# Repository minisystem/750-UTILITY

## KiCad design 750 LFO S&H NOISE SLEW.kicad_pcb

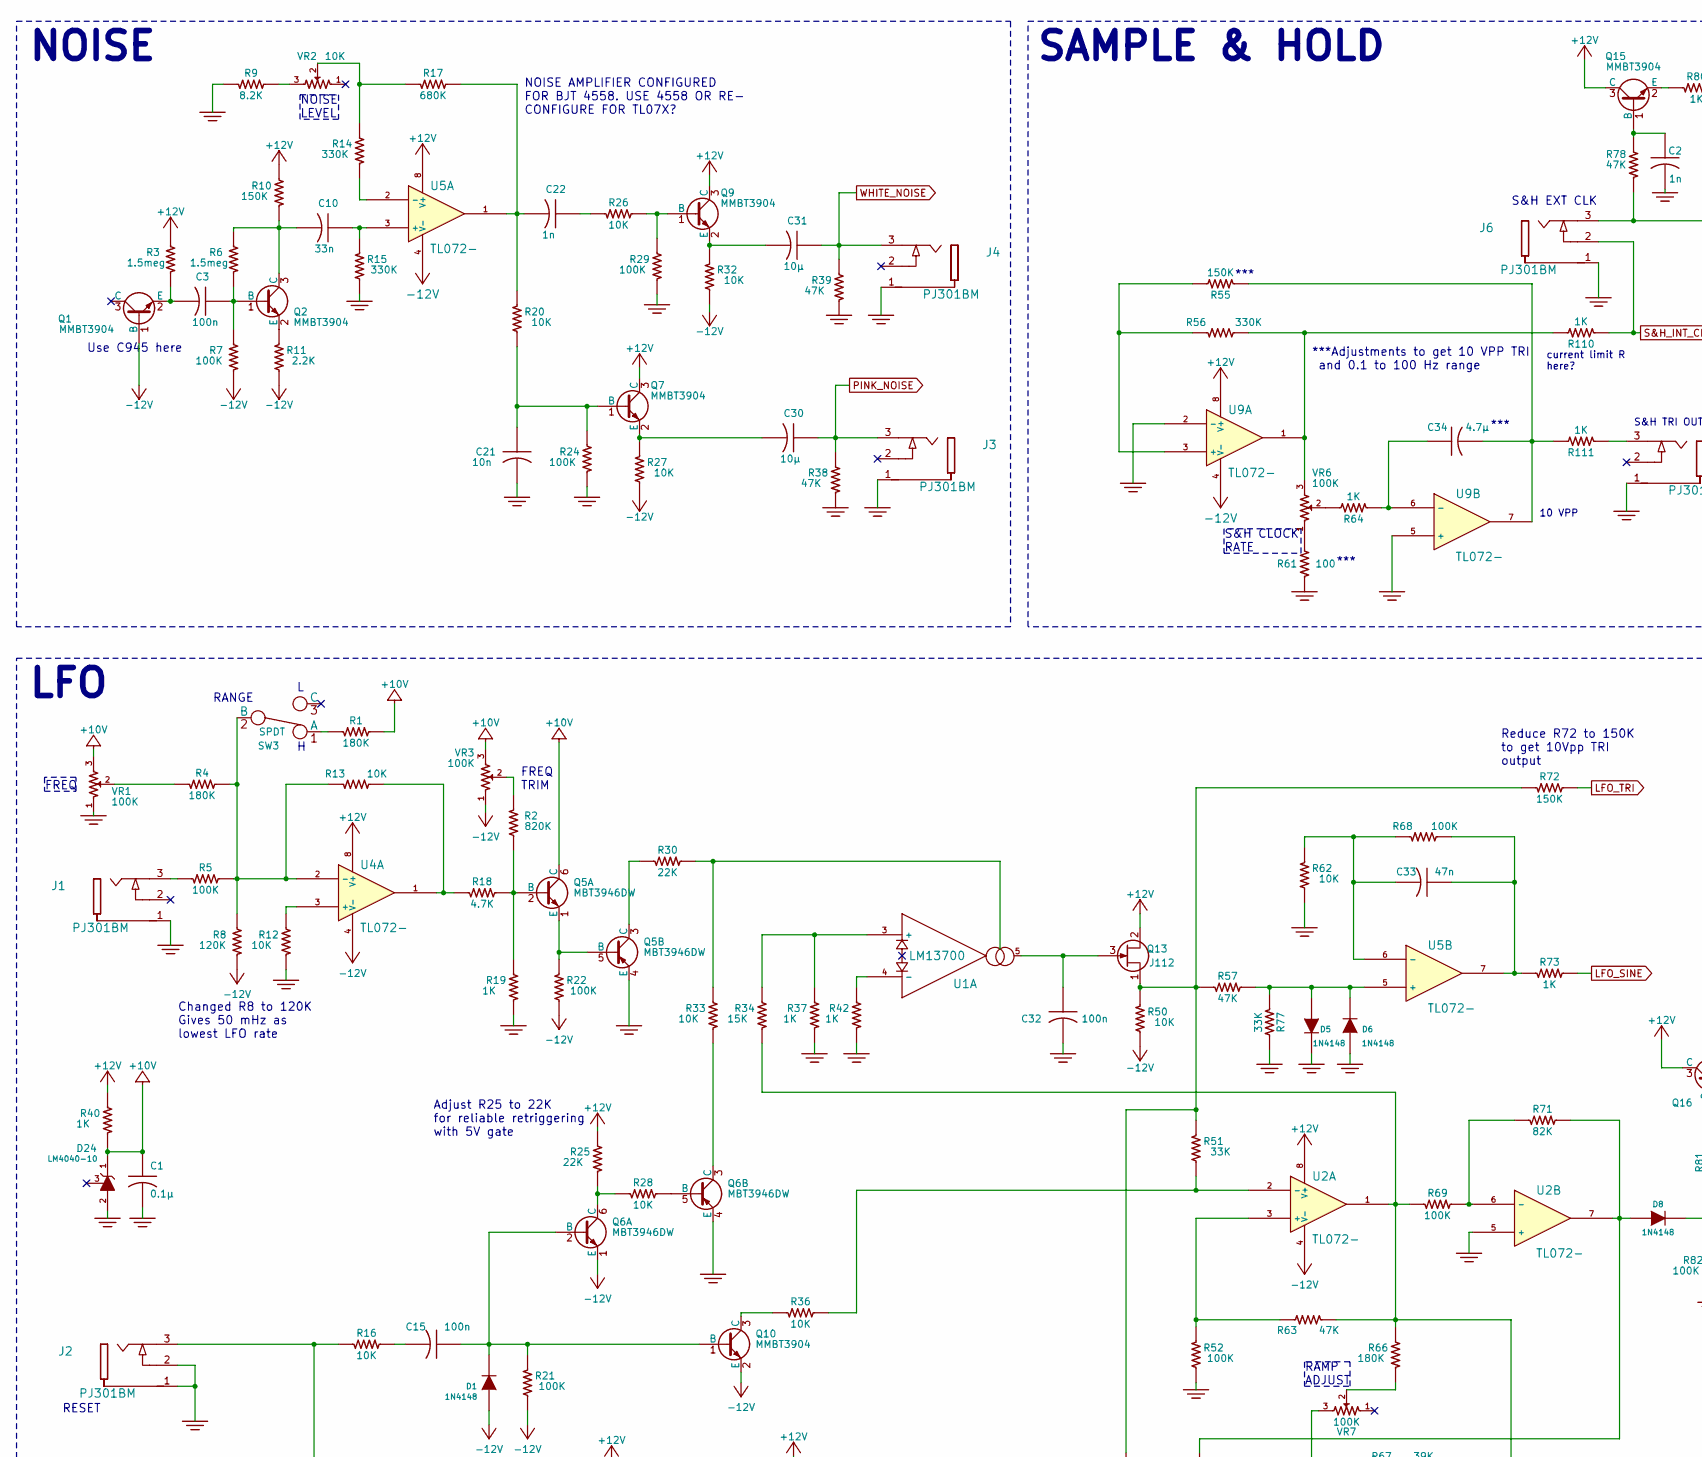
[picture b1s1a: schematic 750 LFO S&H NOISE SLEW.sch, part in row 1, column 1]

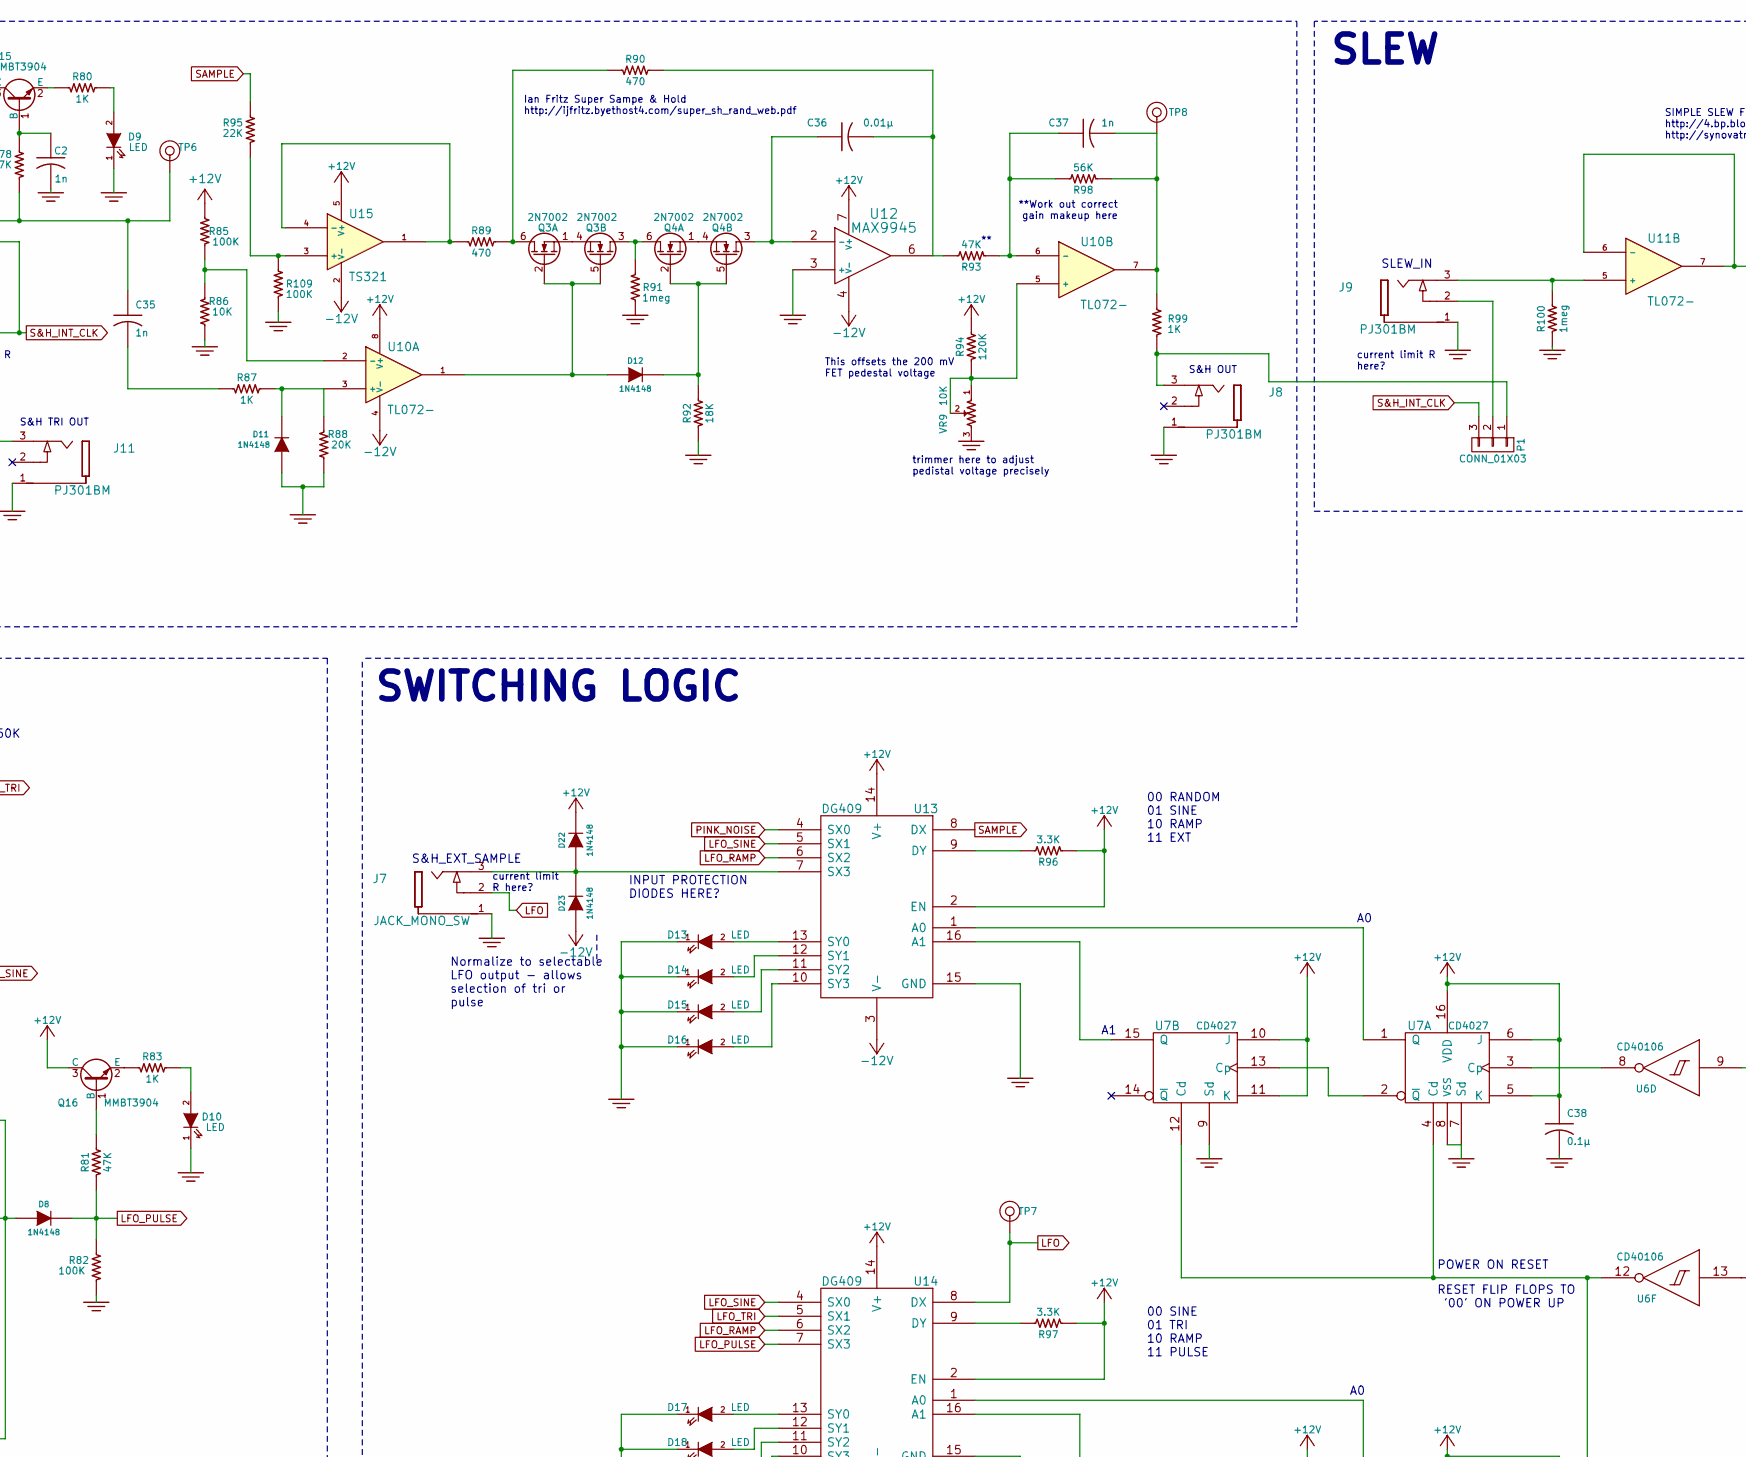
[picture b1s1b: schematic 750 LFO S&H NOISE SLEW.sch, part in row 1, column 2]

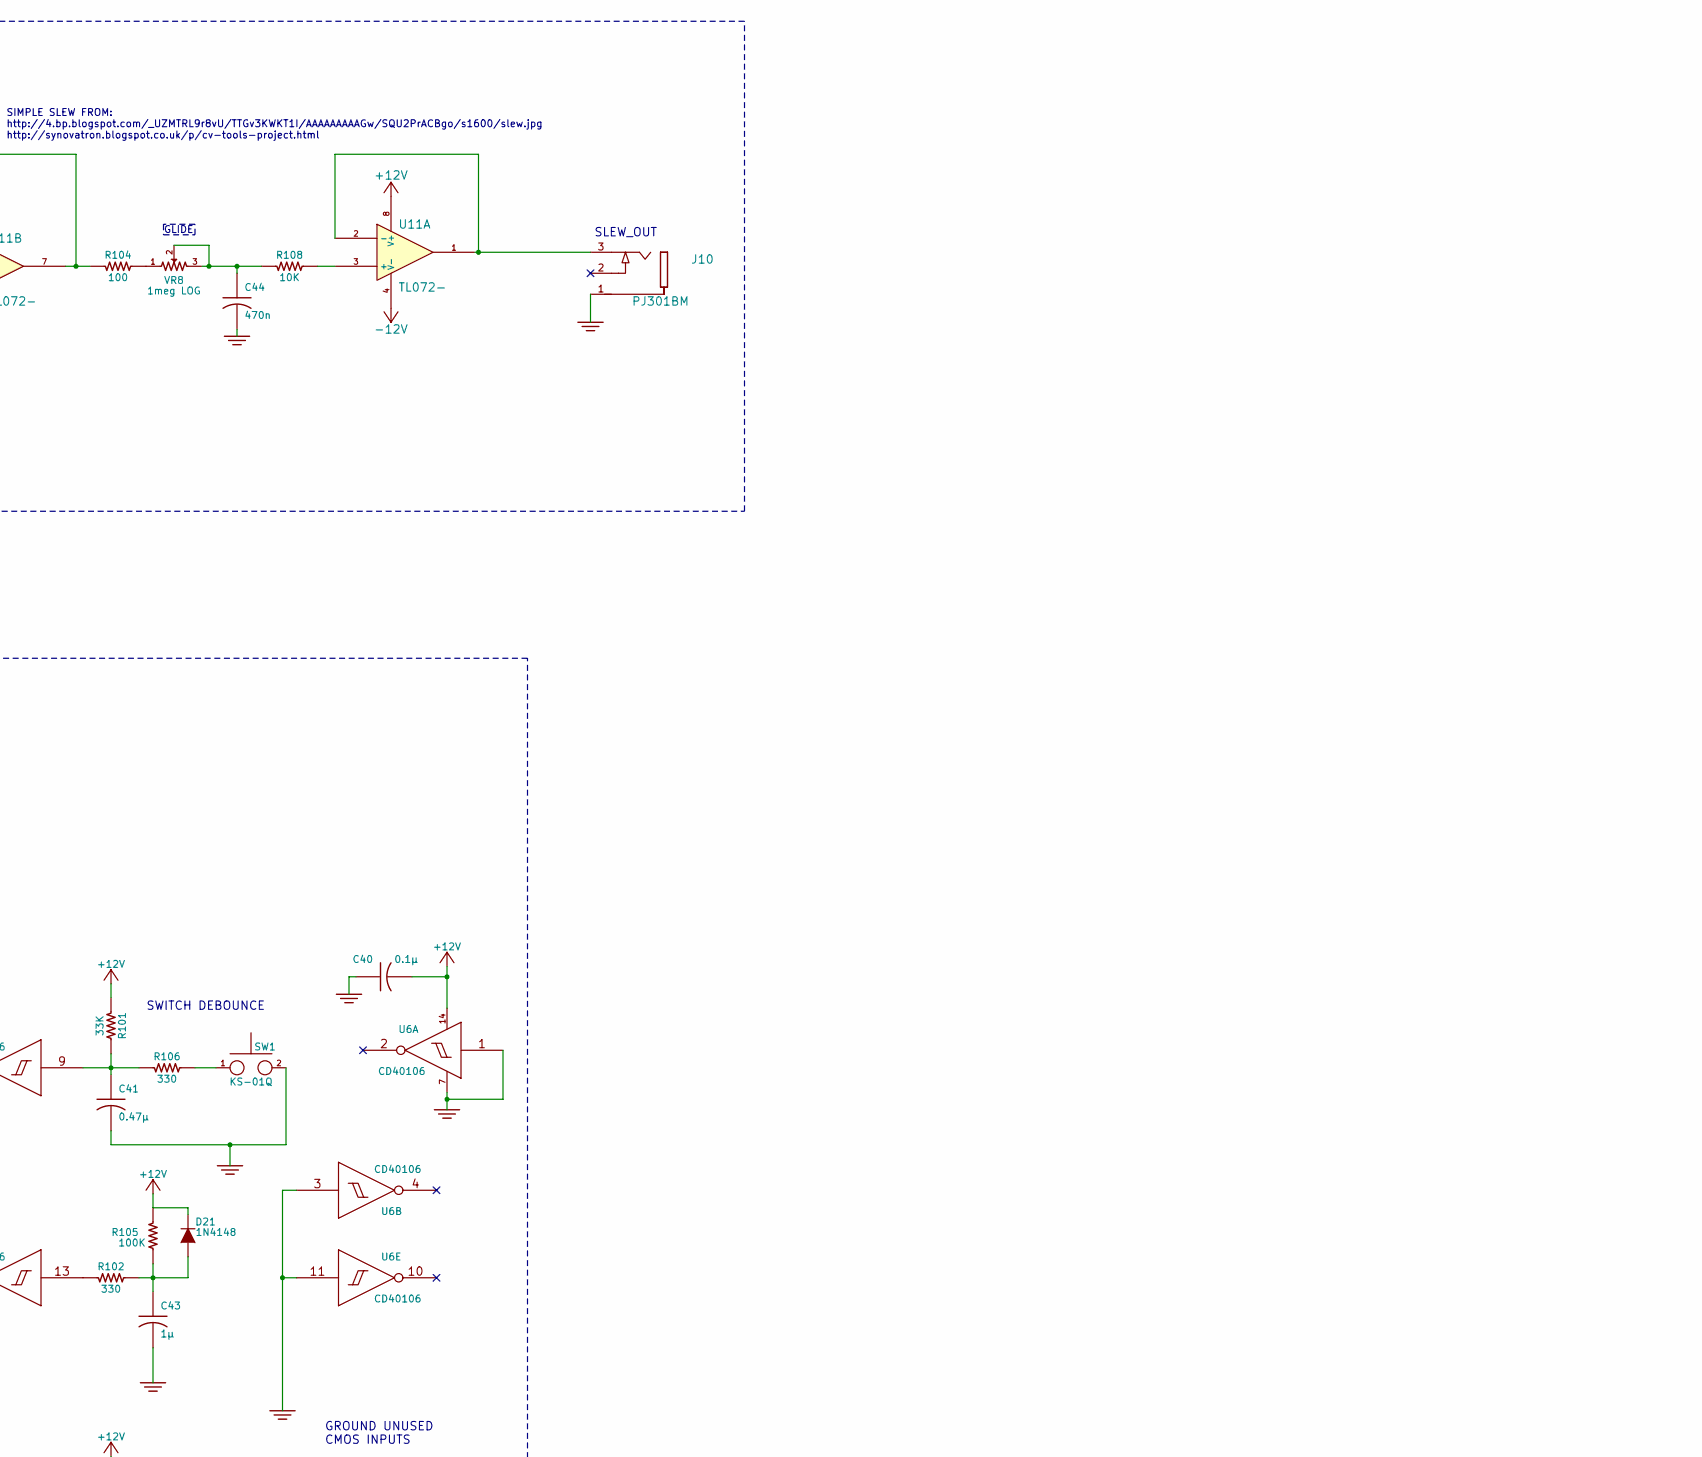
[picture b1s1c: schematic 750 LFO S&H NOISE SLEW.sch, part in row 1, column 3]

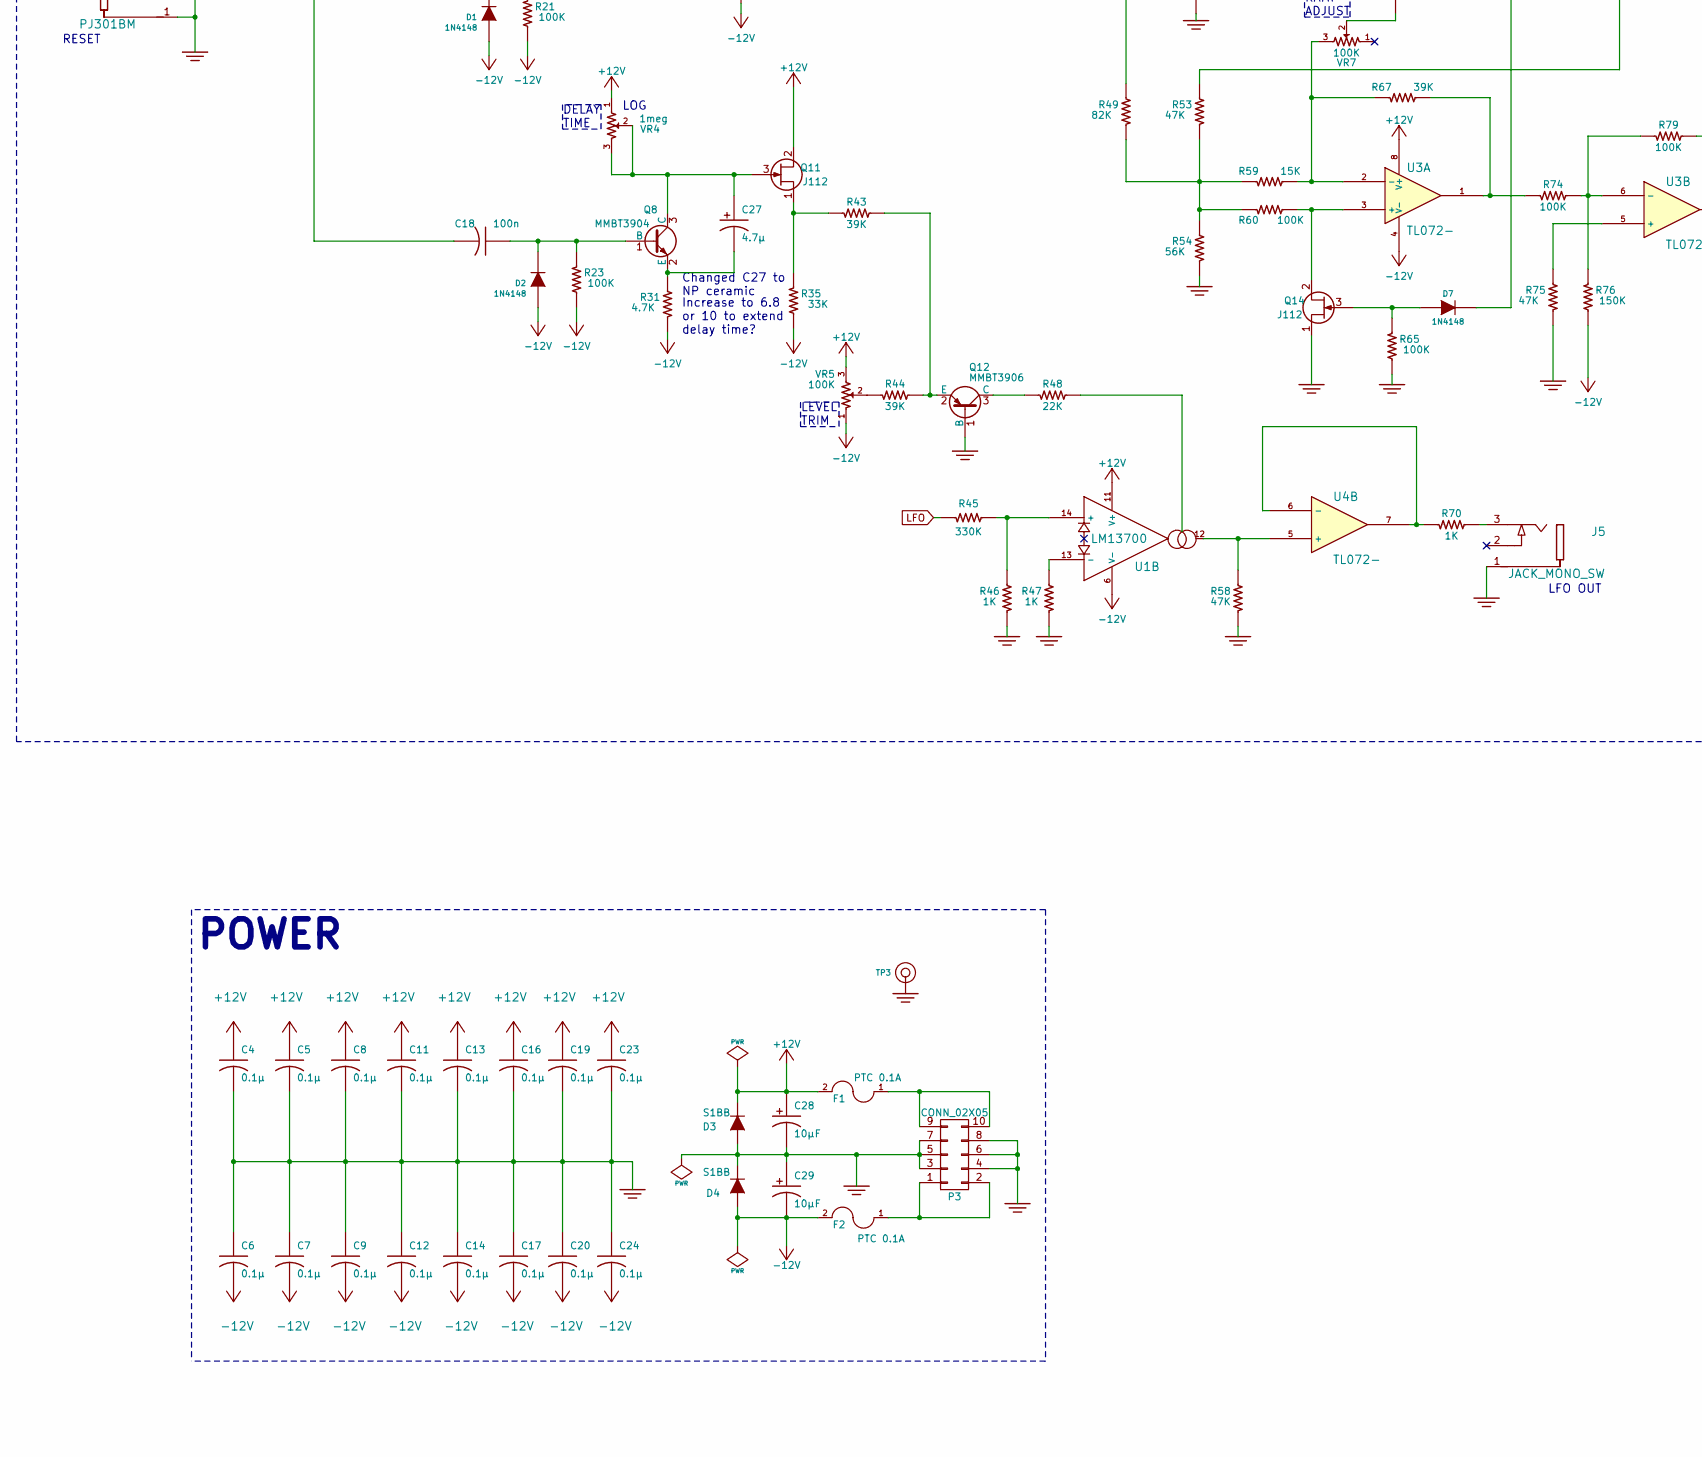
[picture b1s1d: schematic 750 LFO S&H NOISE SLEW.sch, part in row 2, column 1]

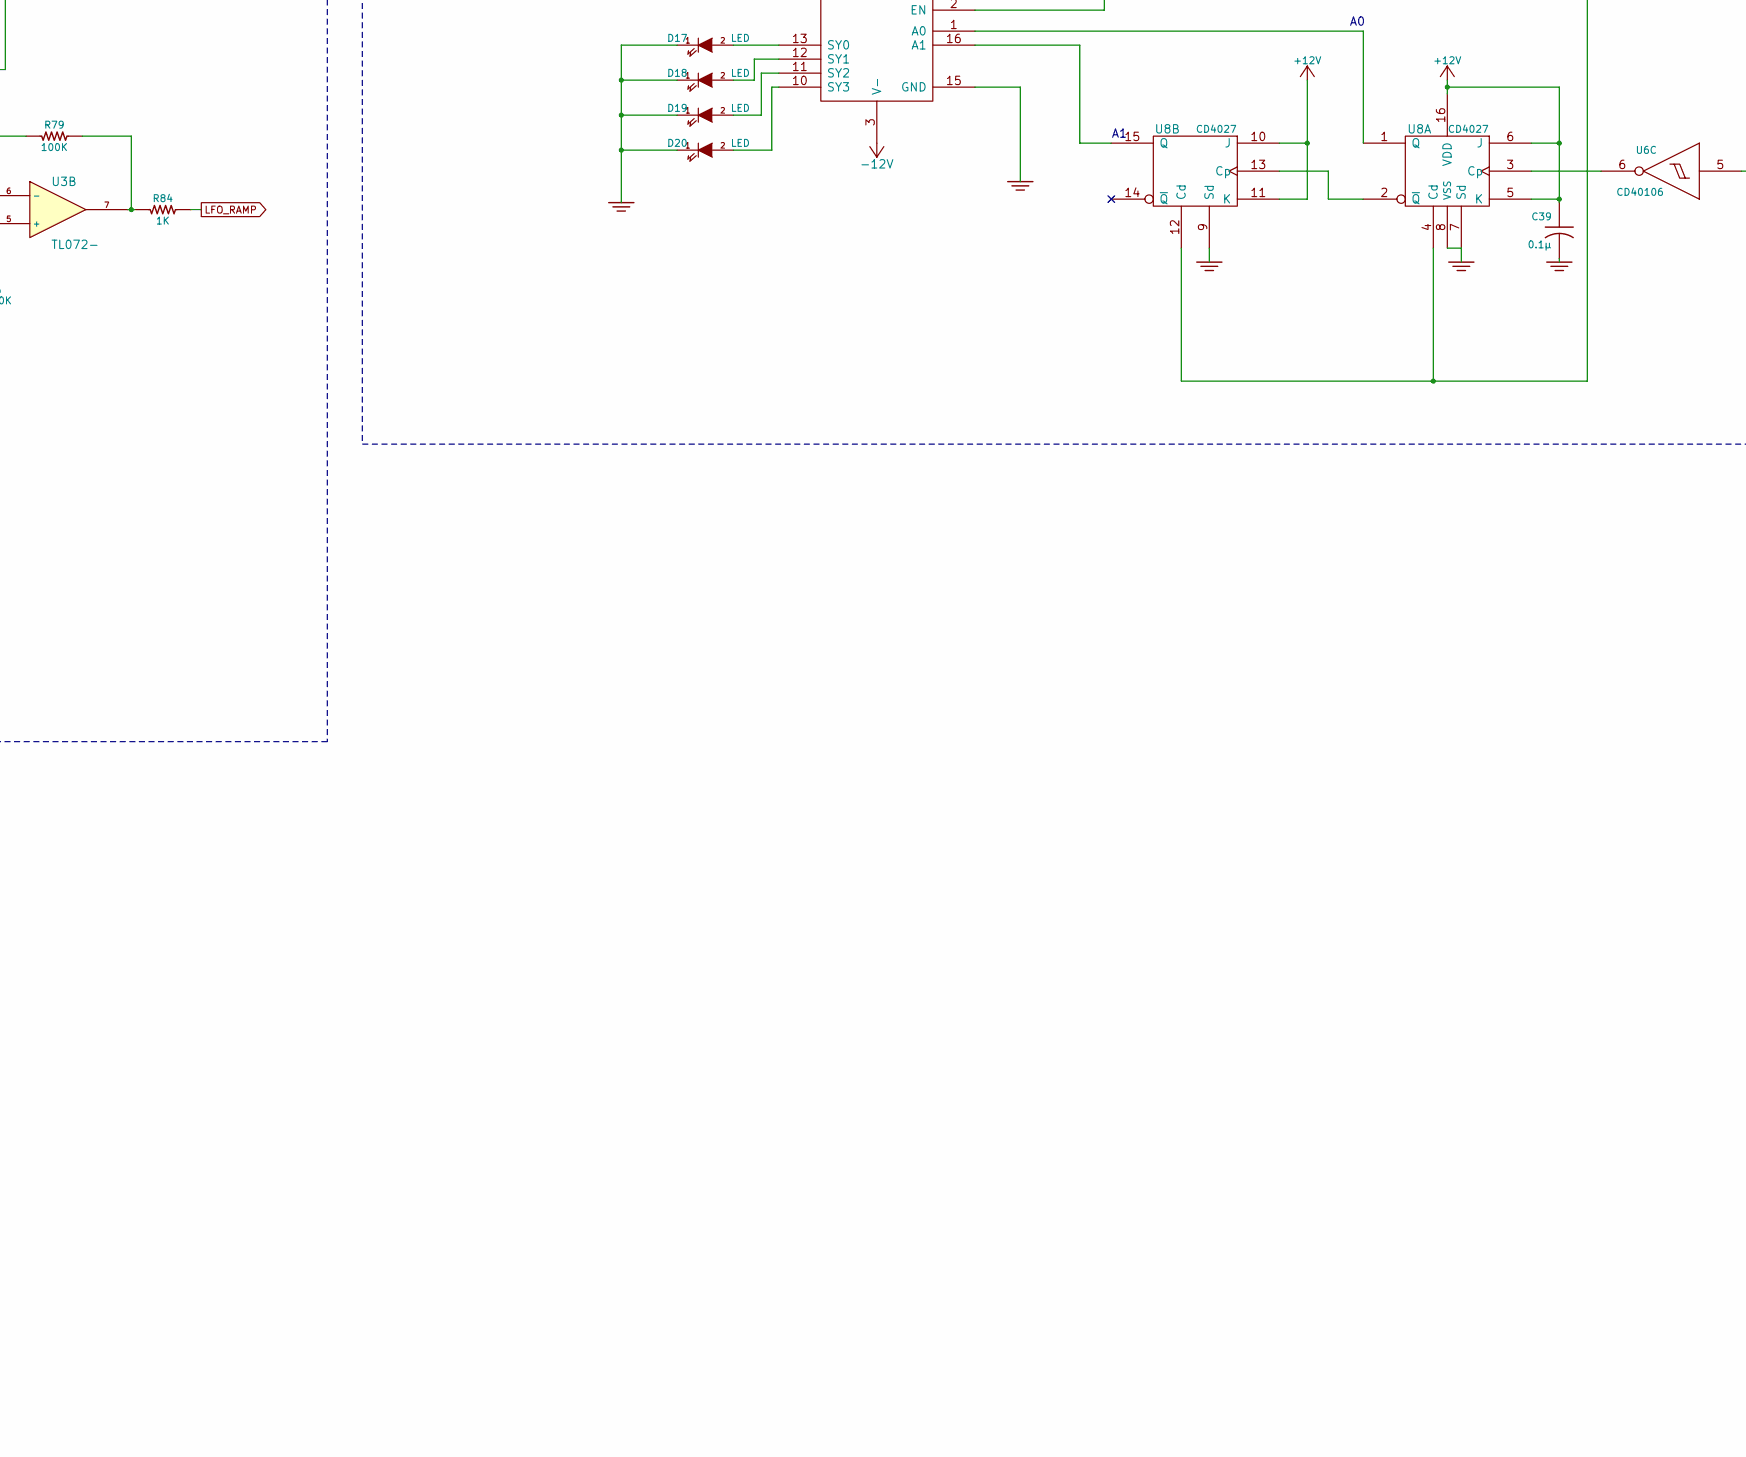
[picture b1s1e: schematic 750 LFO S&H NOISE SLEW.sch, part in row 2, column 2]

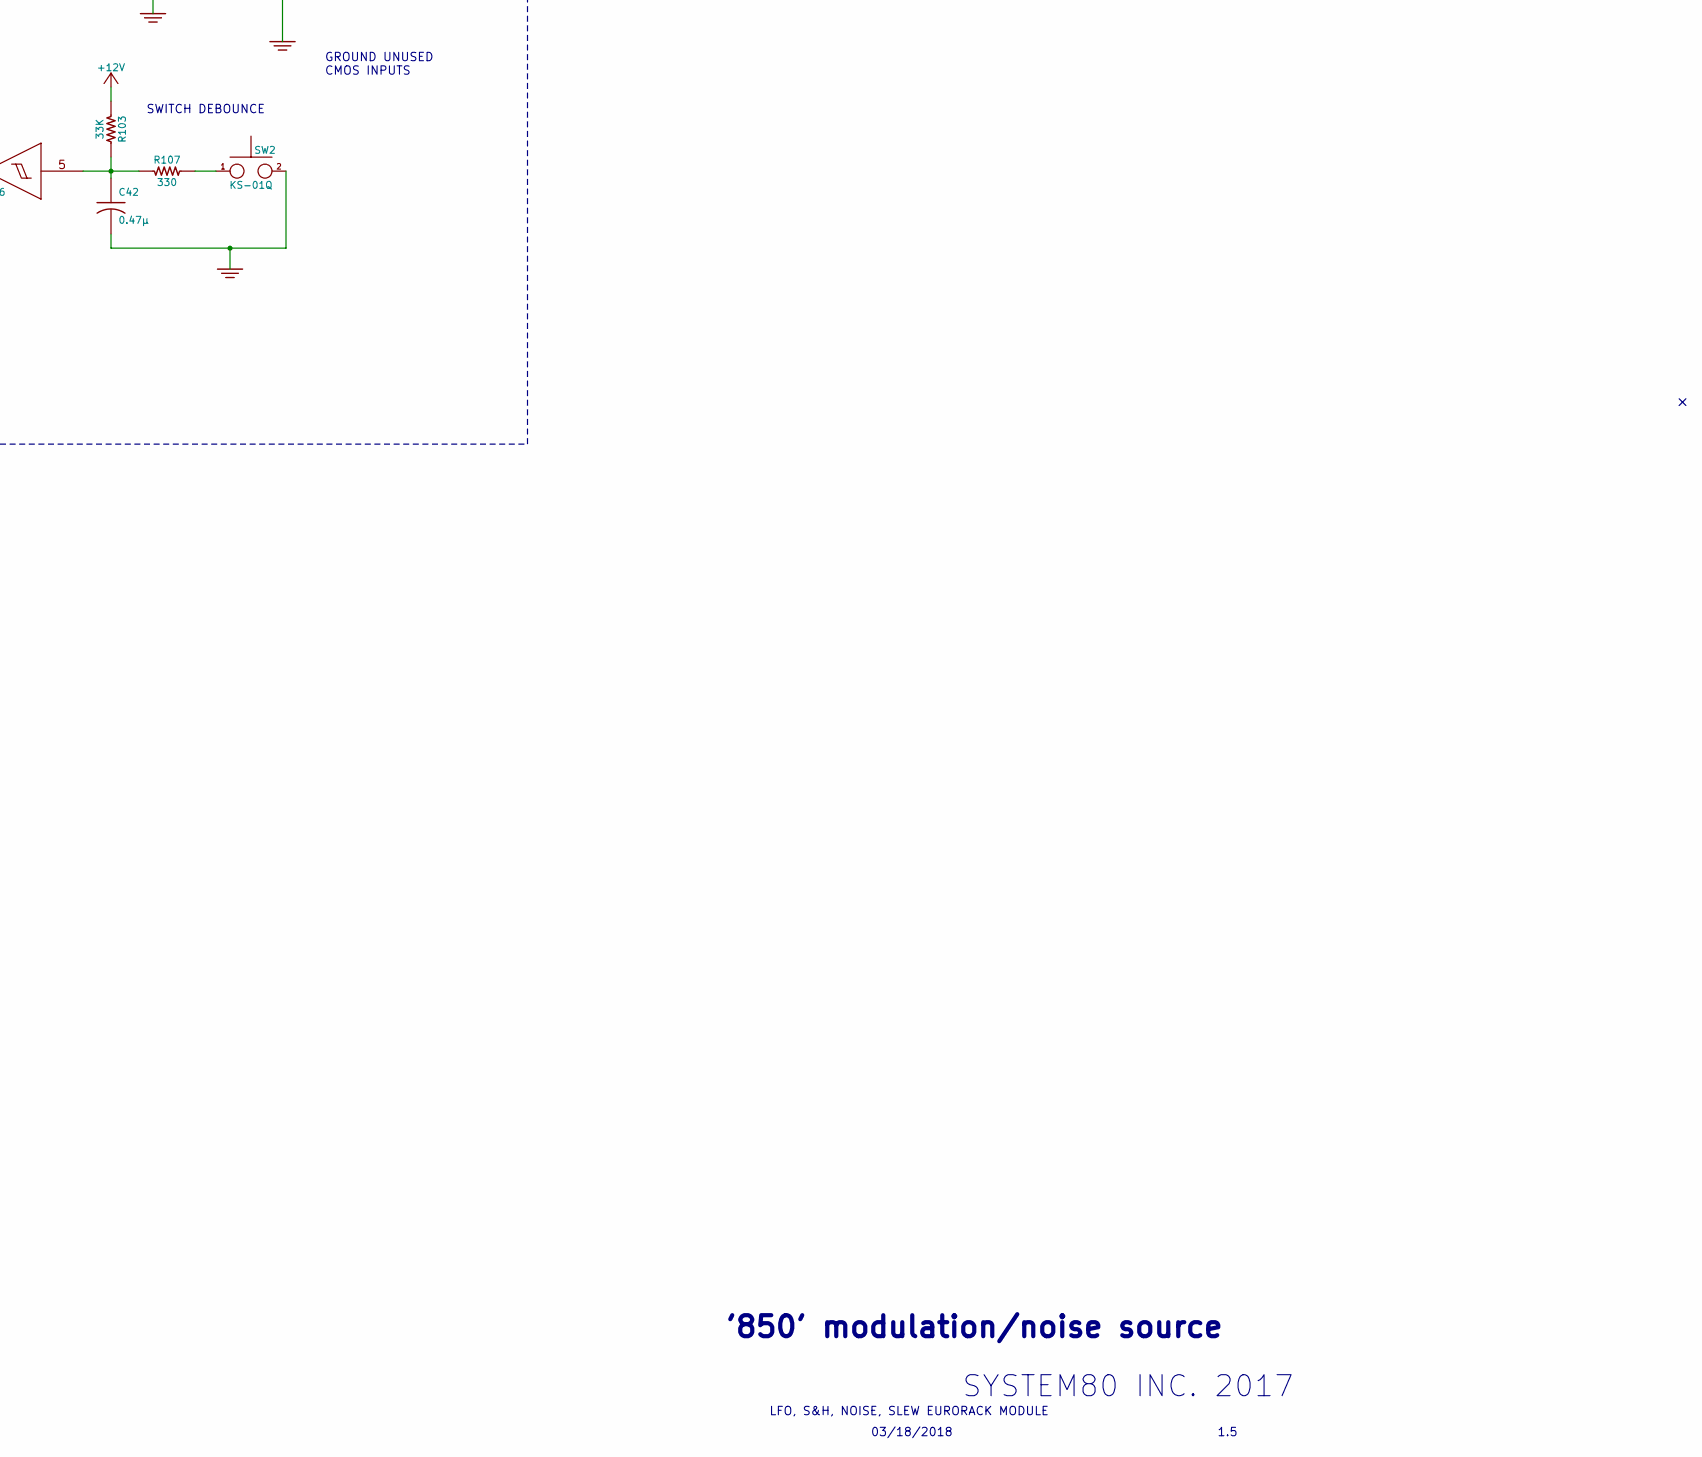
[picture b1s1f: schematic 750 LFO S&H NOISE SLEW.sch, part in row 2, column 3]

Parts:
C1, C4, C5, C6, C7, C8, C9, C11, C12, C13, C14, C16, C17, C19, C20, C23, C24, C38, C39, C40: 0.1µ; SM0603-C-JRL
C2, C22, C35, C37: 1n; SM0603-C-JRL
C3, C15, C18, C32: 100n; SM0603-C-JRL
C10: 33n; SM0603-C-JRL
C21: 10n; SM0603-C-JRL
C27, C34: 4.7μ; SM0805-HAND
C28, C29: 10μF; c_elec_5x5.3
C30, C31: 10μ; SM0805-HAND
C33: 47n; SM0603-C-JRL
C36: 0.01μ; SM0603-C-JRL
C41, C42: 0.47μ; SM0603-C-JRL
C43: 1μ; SM0603-C-JRL
C44: 470n; CAP-5MM-BOX-0805-COMBO
D1, D2, D5, D6, D7, D8, D11, D12, D22, D23: 1N4148; SOD323-JRL
D3, D4: S1BB; SMB-1C2A
D9, D10, D13, D14, D15, D16, D17, D18, D19, D20: LED; 3MM-LED-C1A2
D21: 1N4148; SOD323-C1A2
D24: LM4040-10; SOT23-132-JRL
F1, F2: PTC 0.1A; C_0805
J1, J2, J3, J4, J6, J8, J9, J10, J11: PJ301BM; PJ-301B-JACK-SLOTS
J5, J7: JACK_MONO_SW; PJ-301B-JACK-SLOTS
P1: CONN_01X03; PAD_3
P3: CONN_02X05; Pin_Header_Straight_2x05
Q1, Q2, Q7, Q8, Q9, Q10, Q15, Q16: MMBT3904; SOT23-132-JRL
Q3, Q4: 2N7002; SOT363-JRL
Q5, Q6: MBT3946DW; SOT363-JRL
Q11, Q13, Q14: J112; SOT23-JRL
Q12: MMBT3906; SOT23-132-JRL
R1, R4, R66: 180K; SM0603-R-JRL
R2: 820K; SM0603-R-JRL
R3, R6: 1.5meg; SM0603-R-JRL
R5, R7, R21, R22, R23, R24, R29, R52, R60, R65, R68, R69, R74, R79, R82, R85, R105, R109: 100K; SM0603-R-JRL
R8, R94: 120K; SM0603-R-JRL
R9: 8.2K; SM0603-R-JRL
R10, R55, R72, R76: 150K; SM0603-R-JRL
R11: 2.2K; SM0603-R-JRL
R12, R13, R16, R20, R26, R27, R28, R32, R33, R36, R50, R62, R86, R108: 10K; SM0603-R-JRL
R14, R15, R45, R56: 330K; SM0603-R-JRL
R17: 680K; SM0603-R-JRL
R18, R31: 4.7K; SM0603-R-JRL
R19, R37, R40, R42, R46, R47, R64, R70, R73, R80, R83, R84, R87, R99, R110, R111: 1K; SM0603-R-JRL
R25, R30, R48, R95: 22K; SM0603-R-JRL
R34, R59: 15K; SM0603-R-JRL
R35, R51, R77, R101, R103: 33K; SM0603-R-JRL
R38, R39, R53, R57, R58, R63, R75, R78, R81, R93: 47K; SM0603-R-JRL
R43, R44, R67: 39K; SM0603-R-JRL
R49, R71: 82K; SM0603-R-JRL
R54, R98: 56K; SM0603-R-JRL
R61, R104: 100; SM0603-R-JRL
R88: 20K; SM0603-R-JRL
R89, R90: 470; SM0603-R-JRL
R91, R100: 1meg; SM0603-R-JRL
R92: 18K; SM0603-R-JRL
R96, R97: 3.3K; SM0603-R-JRL
R102, R106, R107: 330; SM0603-R-JRL
SW1, SW2: KS-01Q; KS-01Q-02-JRL
SW3: SPDT; SS-12F45-1P2T-SLIDE
TP3: CONN_1; TEST_POINT_LOOP_4592
TP6, TP7, TP8: CONN_1; TEST_POINT_SMALL
U1: LM13700; SO16-JRL
U2, U3, U4, U5, U9, U10, U11: TL072-; TSSOP8-JRL
U6: CD40106; TSSOP-14_4.4x5mm_Pitch0.65mm
U7, U8: CD4027; TSSOP-16_4.4x5mm_Pitch0.65mm
U12: MAX9945; MSOP-8_3x3mm_Pitch0.65mm
U13, U14: DG409; SO16-JRL
U15: TS321; SOT-23-5
VR1, VR6: 100K; RV16A-41-JRL
VR2, VR9: 10K; TC33X-2
VR3, VR5, VR7: 100K; TC33X-2
VR4: 1meg; RV16A-41-JRL
VR8: 1meg LOG; RV16A-41-JRL

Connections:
+10V: C1.1, D24.1 (K), Q5.6 (C), R1.2, R40.2, VR1.3, VR3.3
+12V: C4.1, C5.1, C8.1, C11.1, C13.1, C16.1, C19.1, C23.1, C28.1 (+), C38.1, C39.1, C40.2, D3.1 (K), D21.1 (K), D22.2 (K), F1.2, Q7.3 (C), Q9.3 (C), Q11.2 (D), Q13.2 (D), Q15.3 (C), Q16.3 (C), R3.1, R10.1, R25.1, R40.1, R85.2, R94.2, R96.1, R97.1, R101.2, R103.2, R105.2, U1.11 (V+), U2.8 (V+), U3.8 (V+), U4.8 (V+), U5.8 (V+), U6.14 (VDD), U7.5 (K), U7.6 (J), U7.10 (J), U7.11 (K), U7.16 (VDD), U8.5 (K), U8.6 (J), U8.10 (J), U8.11 (K), U8.16 (VDD), U9.8 (V+), U10.8 (V+), U11.8 (V+), U12.7 (V+), U13.2 (EN), U13.14 (V+), U14.2 (EN), U14.14 (V+), U15.5 (V+), VR4.1, VR5.3
-12V: C6.2, C7.2, C9.2, C12.2, C14.2, C17.2, C20.2, C24.2, C29.2 (-), D1.1 (A), D2.1 (A), D4.2 (A), D23.1 (A), F2.2, Q1.1 (B), Q6.1 (E), Q10.2 (E), R7.2, R8.2, R11.2, R21.2, R22.2, R23.2, R27.2, R31.2, R32.2, R35.2, R50.2, R76.2, U1.6 (V-), U2.4 (V-), U3.4 (V-), U4.4 (V-), U5.4 (V-), U9.4 (V-), U10.4 (V-), U11.4 (V-), U12.4 (V-), U13.3 (V-), U14.3 (V-), U15.2 (V-), VR3.1, VR5.1
GND: C1.2, C2.2, C4.2, C5.2, C6.1, C7.1, C8.2, C9.1, C11.2, C12.1, C13.2, C14.1, C16.2, C17.1, C19.2, C20.1, C21.2, C23.2, C24.1, C28.2 (-), C29.1 (+), C32.2, C38.2, C39.2, C40.1, C41.2, C42.2, C43.2, C44.2, D3.2 (A), D4.1 (K), D5.2 (K), D6.1 (A), D9.1 (K), D10.1 (K), D11.1 (A), D13.1 (K), D14.1 (K), D15.1 (K), D16.1 (K), D17.1 (K), D18.1 (K), D19.1 (K), D20.1 (K), D24.2 (A), J1.1, J2.1, J2.2, J3.1, J4.1, J5.1, J6.1, J7.1, J8.1, J9.1, J10.1, J11.1, P3.3, P3.4, P3.5, P3.6, P3.7, P3.8, Q5.4 (E), Q6.4 (E), Q12.1 (B), Q14.1 (S), R9.1, R12.2, R15.2, R19.2, R24.2, R29.2, R37.2, R38.2, R39.2, R42.2, R46.2, R47.2, R52.2, R54.2, R58.2, R61.1, R62.2, R65.2, R75.2, R77.2, R82.2, R86.2, R88.2, R91.2, R92.1, R100.2, R109.1, SW1.2, SW2.2, TP3.1, U2.5 (+), U6.1 (In), U6.3 (In), U6.7 (VSS), U6.11 (In), U7.7 (Sd), U7.8 (VSS), U7.9 (Sd), U8.7 (Sd), U8.8 (VSS), U8.9 (Sd), U9.2 (-), U9.5 (+), U12.3 (+), U13.15 (GND), U14.15 (GND), VR1.1, VR9.3
LFO: J7.2, R45.2, TP7.1, U14.8 (DX)
LFO_PULSE: D8.2 (K), R81.1, R82.1, U14.7 (SX3)
LFO_RAMP: R84.2, U13.6 (SX2), U14.6 (SX2)
LFO_SINE: R73.2, U13.5 (SX1), U14.4 (SX0)
LFO_TRI: R72.2, U14.5 (SX1)
unnamed: C2.1, Q15.1 (B), R78.2
unnamed: C3.1, Q2.1 (B), R6.2, R7.1
unnamed: C3.2, Q1.2 (E), R3.2
unnamed: C10.1, R15.1, U5.3 (+)
unnamed: C10.2, Q2.3 (C), R6.1, R10.2
unnamed: C15.1, D1.2 (K), Q6.2 (B), Q10.1 (B), R21.1
unnamed: C15.2, R16.2
unnamed: C18.1, D2.2 (K), Q8.1 (B), R23.1
unnamed: C18.2, J2.3, R16.1
unnamed: C21.1, Q7.1 (B), R20.2, R24.1
unnamed: C22.1, R26.1
unnamed: C22.2, R17.2, R20.1, U5.1
unnamed: C27.1 (+), Q8.3 (C), Q11.3 (G), VR4.2, VR4.3
unnamed: C27.2 (-), Q8.2 (E), R31.1
unnamed: C30.2, Q7.2 (E), R27.1
unnamed: C31.2, Q9.2 (E), R32.1
unnamed: C32.1, Q13.3 (G), U1.5
unnamed: C33.1, R68.2, R73.1, U5.7
unnamed: C33.2, R62.1, R68.1, U5.6 (-)
unnamed: C34.1, R64.1, U9.6 (-)
unnamed: C34.2, R55.1, R111.2, U9.7
unnamed: C35.1, J6.3, R78.1, TP6.1
unnamed: C35.2, R87.1
unnamed: C36.1, Q4.3 (D), U12.2 (-)
unnamed: C36.2, R90.1, R93.2, U12.6
unnamed: C37.1, R93.1, R98.2, U10.6 (-)
unnamed: C37.2, R98.1, R99.2, TP8.1, U10.7
unnamed: C41.1, R101.1, R106.1, U6.9 (In)
unnamed: C42.1, R103.1, R107.1, U6.5 (In)
unnamed: C43.1, D21.2 (A), R102.2, R105.1
unnamed: C44.1, R108.2, VR8.2, VR8.3
unnamed: D5.1 (A), D6.2 (K), R57.2, R77.1, U5.5 (+)
unnamed: D7.1 (A), Q14.3 (G), R65.1
unnamed: D7.2 (K), R34.2, R63.2, R66.1, R69.1, U2.1
unnamed: D8.1 (A), R53.1, R71.2, U2.7
unnamed: D9.2 (A), R80.2
unnamed: D10.2 (A), R83.2
unnamed: D11.2 (K), R87.2, R88.1, U10.3 (+)
unnamed: D12.1 (A), Q3.2 (G), Q3.5 (G), U10.1
unnamed: D12.2 (K), Q4.2 (G), Q4.5 (G), R92.2
unnamed: D13.2 (A), U13.13 (SY0)
unnamed: D14.2 (A), U13.12 (SY1)
unnamed: D15.2 (A), U13.11 (SY2)
unnamed: D16.2 (A), U13.10 (SY3)
unnamed: D17.2 (A), U14.13 (SY0)
unnamed: D18.2 (A), U14.12 (SY1)
unnamed: D19.2 (A), U14.11 (SY2)
unnamed: D20.2 (A), U14.10 (SY3)
unnamed: D22.1 (A), D23.2 (K), J7.3, U13.7 (SX3)
unnamed: F1.1, P3.9, P3.10
unnamed: F2.1, P3.1, P3.2
unnamed: J1.3, R5.1
unnamed: J5.3, R70.2
unnamed: J8.3, P1.1, R99.1
unnamed: J9.2, P1.2
unnamed: J9.3, R100.1, U11.5 (+)
unnamed: J10.3, U11.1, U11.2 (-)
unnamed: J11.3, R111.1
unnamed: Q2.2 (E), R11.1
unnamed: Q3.1 (S), Q3.4 (S)
unnamed: Q3.3 (D), Q4.6 (D), R91.1
unnamed: Q3.6 (D), R89.1, R90.2
unnamed: Q4.1 (S), Q4.4 (S)
unnamed: Q5.1 (E), Q5.5 (B), R22.1
unnamed: Q5.2 (B), R2.2, R18.2, R19.1
unnamed: Q5.3 (C), R30.1
unnamed: Q6.3 (C), R33.2
unnamed: Q6.5 (B), R28.2
unnamed: Q6.6 (C), R25.2, R28.1
unnamed: Q9.1 (B), R26.2, R29.1
unnamed: Q10.3 (C), R36.1
unnamed: Q11.1 (S), R35.1, R43.1
unnamed: Q12.2 (E), R43.2, R44.2
unnamed: Q12.3 (C), R48.1
unnamed: Q13.1 (S), R49.1, R50.1, R51.1, R57.1, R72.1
unnamed: Q14.2 (D), R60.2, U3.3 (+)
unnamed: Q15.2 (E), R80.1
unnamed: Q16.1 (B), R81.2
unnamed: Q16.2 (E), R83.1
unnamed: R1.1, SW3.1 (A)
unnamed: R2.1, VR3.2
unnamed: R4.1, VR1.2
unnamed: R9.2, VR2.3
unnamed: R12.1, U4.3 (+)
unnamed: R4.2, R5.2, R8.1, R13.1, SW3.2 (B), U4.2 (-)
unnamed: R13.2, R18.1, U4.1
unnamed: R14.1, R17.1, VR2.2
unnamed: R14.2, U5.2 (-)
unnamed: R30.2, R33.1, U1.1
unnamed: R34.1, R37.1, U1.3 (+)
unnamed: R36.2, R51.2, U2.2 (-)
unnamed: R42.1, U1.4 (-)
unnamed: R44.1, VR5.2
unnamed: R45.1, R46.1, U1.14 (+)
unnamed: R47.1, U1.13 (-)
unnamed: R48.2, U1.16
unnamed: R49.2, R53.2, R54.1, R59.1, R60.1
unnamed: R52.1, R63.1, U2.3 (+)
unnamed: R55.2, R56.2, U9.3 (+)
unnamed: R58.1, U1.12, U4.5 (+)
unnamed: R59.2, R67.1, U3.2 (-), VR7.3
unnamed: R61.2, VR6.1
unnamed: R64.2, VR6.2
unnamed: R66.2, VR7.2
unnamed: R67.2, R74.1, U3.1
unnamed: R69.2, R71.1, U2.6 (-)
unnamed: R70.1, U4.6 (-), U4.7
unnamed: R74.2, R76.1, R79.1, U3.6 (-)
unnamed: R75.1, U3.5 (+)
unnamed: R79.2, R84.1, U3.7
unnamed: R85.1, R86.1, U10.2 (-)
unnamed: R89.2, U15.1, U15.4 (-)
unnamed: R94.1, U10.5 (+), VR9.1, VR9.2
unnamed: R96.2, U13.9 (DY)
unnamed: R97.2, U14.9 (DY)
unnamed: R102.1, U6.13 (In)
unnamed: R104.1, VR8.1
unnamed: R104.2, U11.6 (-), U11.7
unnamed: R106.2, SW1.1
unnamed: R107.2, SW2.1
unnamed: R108.1, U11.3 (+)
unnamed: R95.1, R109.2, U15.3 (+)
unnamed: R56.1, R110.2, U9.1, VR6.3
unnamed: U6.6 (Out), U8.3 (Cp)
unnamed: U6.8 (Out), U7.3 (Cp)
unnamed: U6.12 (Out), U7.4 (Cd), U7.12 (Cd), U8.4 (Cd), U8.12 (Cd)
unnamed: U7.2 (~Q), U7.13 (Cp)
unnamed: U8.2 (~Q), U8.13 (Cp)
unnamed: U7.1 (Q), U13.1 (A0)
unnamed: U7.15 (Q), U13.16 (A1)
unnamed: U8.1 (Q), U14.1 (A0)
unnamed: U8.15 (Q), U14.16 (A1)
PINK_NOISE: C30.1, J3.3, R38.1, U13.4 (SX0)
S&H_INT_CLK: J6.2, P1.3, R110.1
SAMPLE: R95.2, U13.8 (DX)
WHITE_NOISE: C31.1, J4.3, R39.1

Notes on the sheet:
POWER
GLIDE
S&H CLOCK RATE
10 VPP
***
***Adjustments to get 10 VPP TRI and 0.1 to 100 Hz range
This offsets the 200 mV FET pedestal voltage
Ian Fritz Super Sampe & Hold http://ijfritz.byethost4.com/super_sh_rand_web.pdf
SLEW_IN
SIMPLE SLEW FROM: http://4.bp.blogspot.com/_UZMTRL9r8vU/TTGv3KWKT1I/AAAAAAAAAGw/SQU2PrACBgo/s1600/slew.jpg http://synovatron.blogspot.co.uk/p/cv-tools-project.html
S&H EXT CLK
S&H_EXT_SAMPLE
SLEW_OUT
00 RANDOM 01 SINE 10 RAMP 11 EXT
POWER ON RESET
SWITCH DEBOUNCE
GROUND UNUSED CMOS INPUTS
RESET FLIP FLOPS TO '00' ON POWER UP
00 SINE 01 TRI 10 RAMP 11 PULSE
RAMP ADJUST
RESET
LEVEL TRIM
LFO OUT
NOISE
SAMPLE & HOLD
LFO
SWITCHING LOGIC
SLEW
NOISE LEVEL
DELAY TIME
FREQ
S&H OUT
**Work out correct gain makeup here
FREQ TRIM
INPUT PROTECTION DIODES HERE?
Normalize to selectable LFO output - allows selection of tri or pulse
trimmer here to adjust pedistal voltage precisely
Changed R8 to 120K Gives 50 mHz as lowest LFO rate
S&H TRI OUT
RANGE
